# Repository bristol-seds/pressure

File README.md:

## BLE Pressure Sensor

Under development

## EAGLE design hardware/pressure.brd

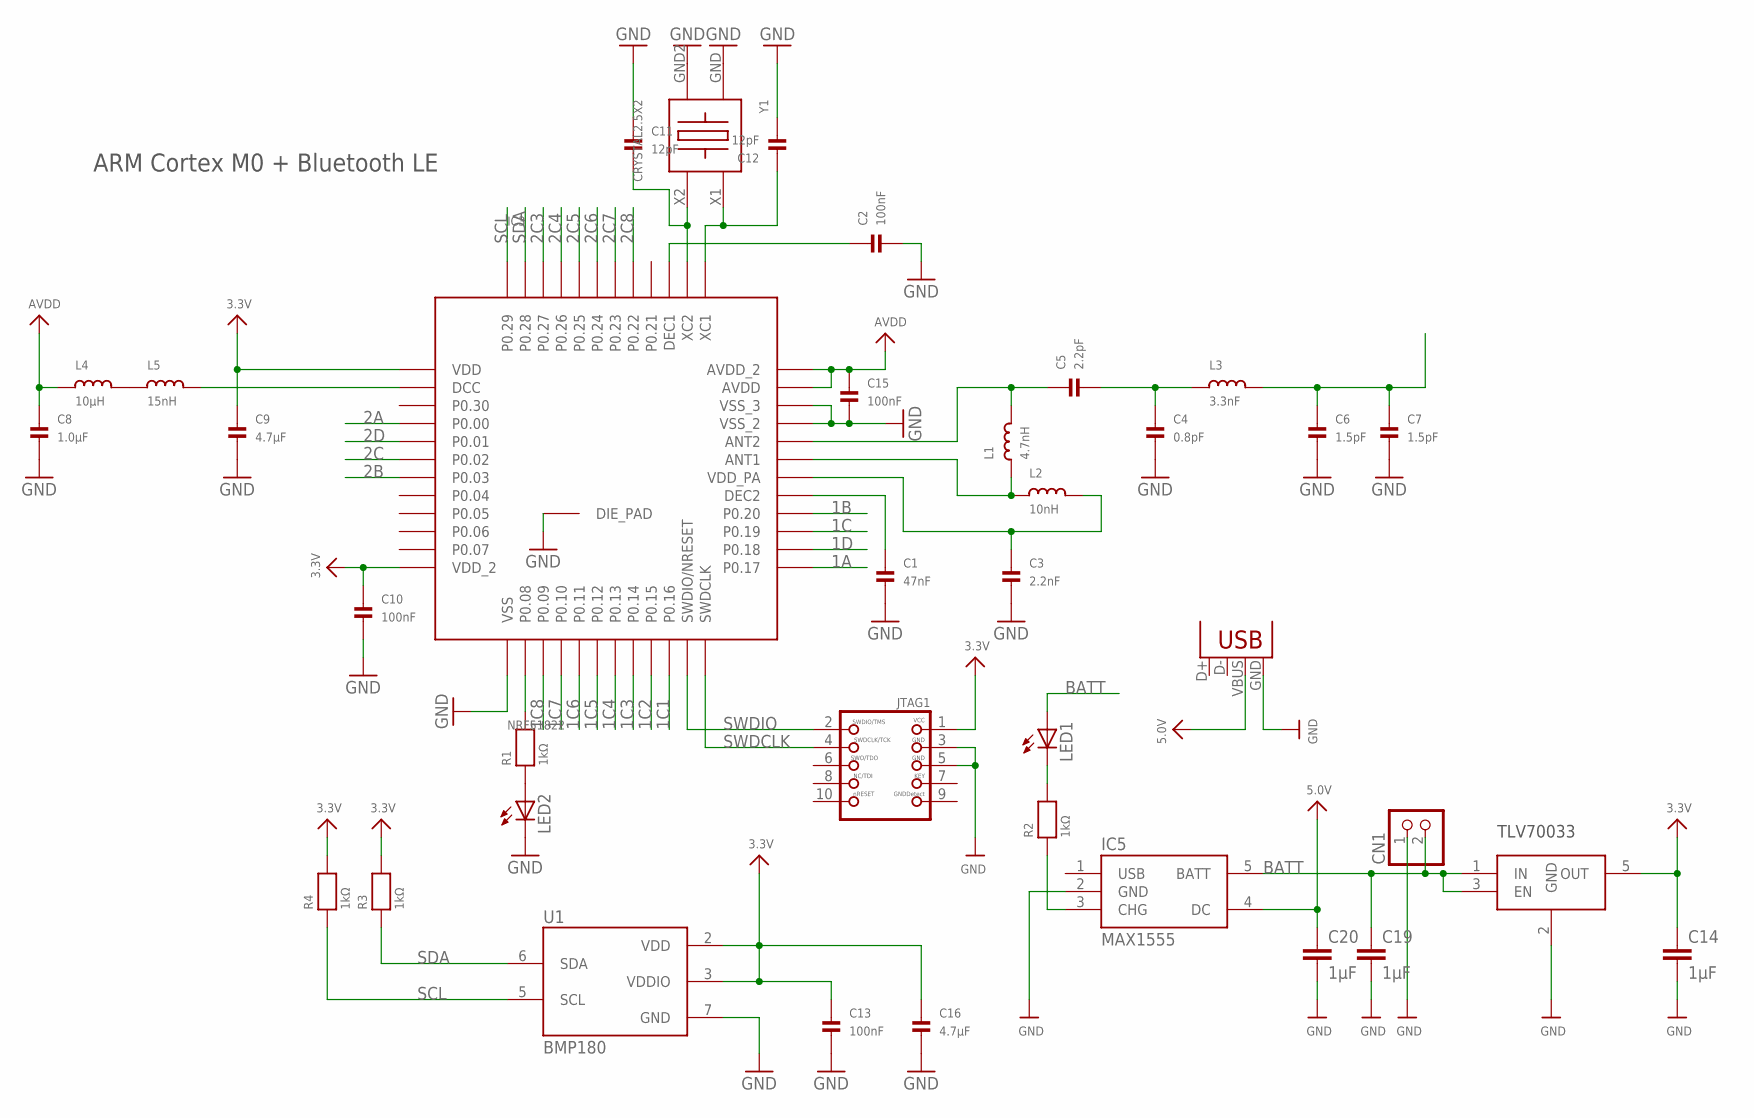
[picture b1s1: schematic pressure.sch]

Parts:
C1: 47nF; _0402
C2, C10, C13, C15: 100nF; _0402
C3: 2.2nF; _0402
C4: 0.8pF; _0402
C5: 2.2pF; _0402
C6, C7: 1.5pF; _0402
C8: 1.0µF; _0402
C9, C16: 4.7µF; _0402
C11, C12: 12pF; _0402
C14, C19, C20: 1µF; C0603K
CN1: JST_2PIN; JSTPH2
IC3: NRF51822; QFN48
IC4: TLV70033DCK; SC70-5L
IC5: MAX1555; SOT23-5
JTAG1: JTAG-CORTEXM3SMT; 2X05_1.27MM_SMT
L1: 4.7nH; _0402
L2: 10nH; _0402
L3: 3.3nF; _0402
L4: 10µH; _0402
L5: 15nH; _0402
LED1, LED2: LEDCHIPLED_0603; CHIPLED_0603
R1, R2, R3, R4: 1kΩ; _0402
U1: BMP180
X1: USB-MICROB
Y1: CRYSTAL2.5X2; 2.5X2MM

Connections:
1A: IC3.25 (P0.17)
1B: IC3.28 (P0.20)
1C: IC3.27 (P0.19)
1C1: IC3.22 (P0.16)
1C2: IC3.21 (P0.15)
1C3: IC3.20 (P0.14)
1C4: IC3.19 (P0.13)
1C5: IC3.18 (P0.12)
1C6: IC3.17 (P0.11)
1C7: IC3.16 (P0.10)
1C8: IC3.15 (P0.09)
1D: IC3.26 (P0.18)
2A: IC3.4 (P0.00)
2B: IC3.7 (P0.03)
2C: IC3.6 (P0.02)
2C3: IC3.46 (P0.27)
2C4: IC3.45 (P0.26)
2C5: IC3.44 (P0.25)
2C6: IC3.43 (P0.24)
2C7: IC3.42 (P0.23)
2C8: IC3.41 (P0.22)
2D: IC3.5 (P0.01)
3.3V: C9.1, C10.1, C13.1, C14.1, C16.1, IC3.1 (VDD), IC3.12 (VDD_2), IC4.5 (OUT), JTAG1.1, R3.2, R4.2, U1.2 (VDD), U1.3 (VDDIO)
5.0V: C20.1, IC5.4 (DC), X1.VBUS
ANT: C6.1, C7.1, L3.2
ANT1: IC3.31 (ANT1), L1.1, L2.1
ANT2: C5.1, IC3.32 (ANT2), L1.2
AVDD: C8.1, C15.1, IC3.35 (AVDD), IC3.36 (AVDD_2), L4.1
BATT: C19.1, CN1.2, IC4.1 (IN), IC4.3 (EN), IC5.5 (BATT), LED1.A
CHG: IC5.3 (CHG), R2.1
DCC: IC3.2 (DCC), L5.2
DEC1: C2.1, IC3.39 (DEC1)
DEC2: C1.1, IC3.29 (DEC2)
GND: C1.2, C2.2, C3.2, C4.2, C6.2, C7.2, C8.2, C9.2, C10.2, C11.1, C12.2, C13.2, C14.2, C15.2, C16.2, C19.2, C20.2, CN1.1, IC3.13 (VSS), IC3.33 (VSS_2), IC3.34 (VSS_3), IC3.GND (DIE_PAD), IC4.2 (GND), IC5.2 (GND), JTAG1.3, JTAG1.5, LED2.C, U1.7 (GND), X1.GND, Y1.GND, Y1.GND2
LED: LED1.C, R2.2
unnamed: L4.2, L5.1
unnamed: IC3.14 (P0.08), R1.2
unnamed: LED2.A, R1.1
SCL: IC3.48 (P0.29), R4.1, U1.5 (SCL)
SDA: IC3.47 (P0.28), R3.1, U1.6 (SDA)
SWDCLK: IC3.24 (SWDCLK), JTAG1.4
SWDIO: IC3.23 (SWDIO/NRESET), JTAG1.2
UNBAL: C4.1, C5.2, L3.1
VDD_PA: C3.1, IC3.30 (VDD_PA), L2.2
X1: C12.1, IC3.37 (XC1), Y1.X1
X2: C11.2, IC3.38 (XC2), Y1.X2

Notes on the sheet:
ARM Cortex M0 + Bluetooth LE
TLV70033

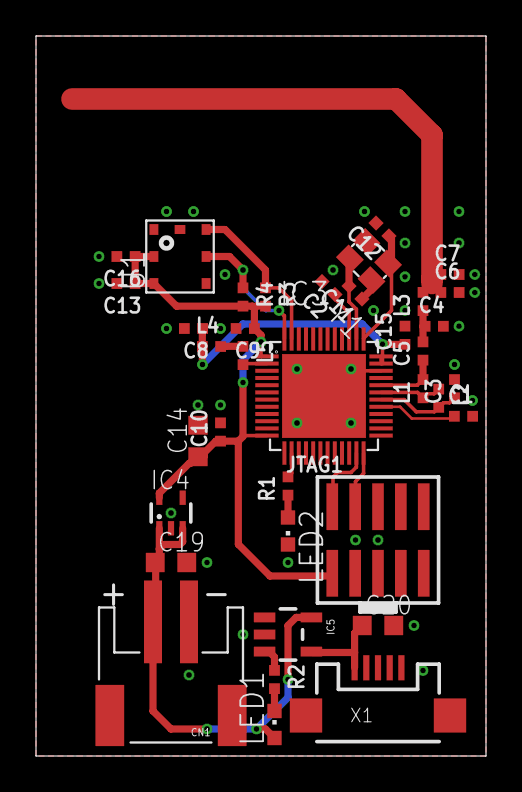
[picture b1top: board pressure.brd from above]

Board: 2 copper layers, 25.0 x 40.0 mm, 37 parts (0 on the bottom side), 24 nets.

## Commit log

2015-03-13 Added partslist
2015-03-13 Added license, readme
2015-03-13 Updated partslist
2015-03-23 Added L4, L5
2015-03-27 Imported toolchain
2015-03-27 Fixed up whatever happened two commits ago...
2015-03-27 Test Hrs app, reading from barometer correctly
2015-03-27 Change ble name
2015-03-28 Added Enviromental Sensing Service (ESS)
2015-03-28 Increased bmp sensing mode type

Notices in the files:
parts and their libraries:
microbuilder_v3: This work is placed in the public domain, and may be freely used for commercial and non-commercial work with the following conditions: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
SparkFun: Licensing: CC v3.0 Share-Alike You are welcome to use this library for commercial purposes.
